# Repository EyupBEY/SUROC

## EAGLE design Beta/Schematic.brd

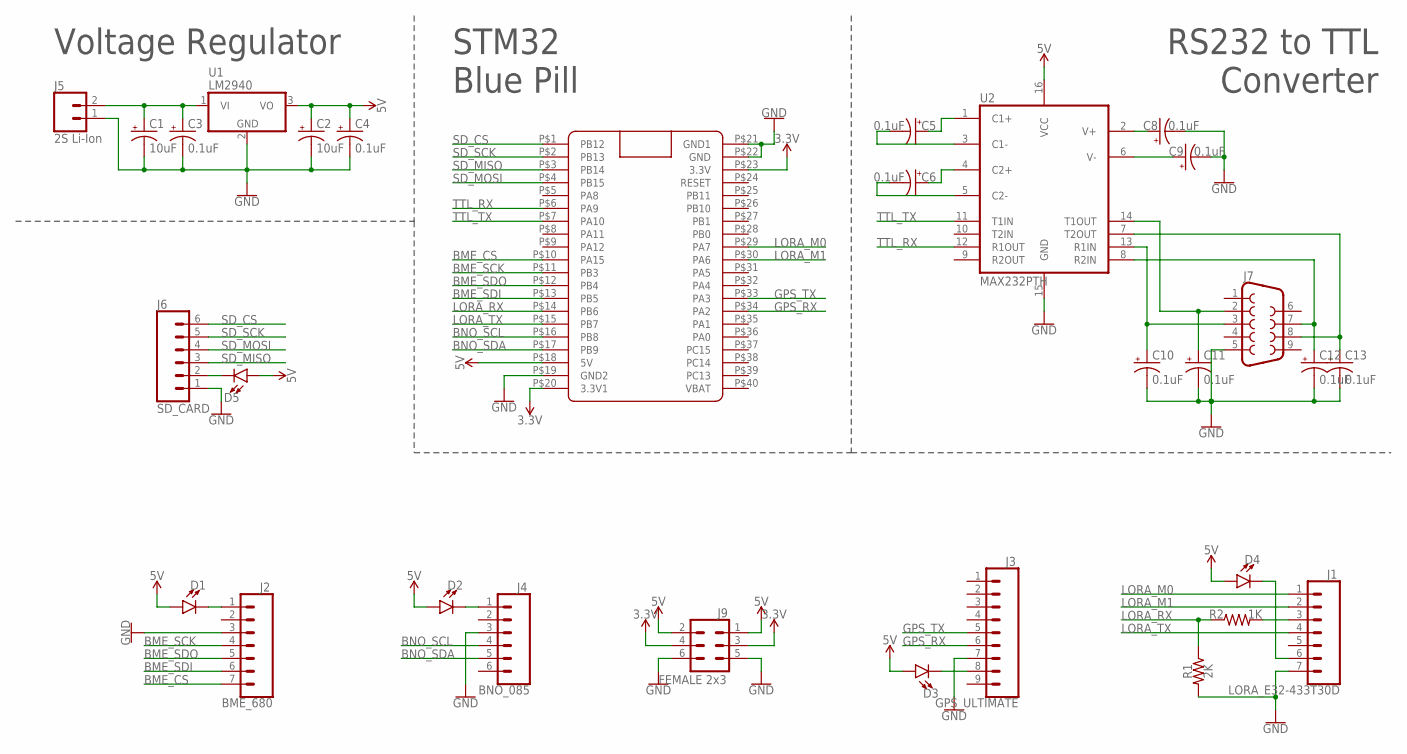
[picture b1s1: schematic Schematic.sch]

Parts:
C1, C2: 10uF; CPOL-RADIAL-2.5MM-5MM-KIT
C3, C4, C5, C6, C8, C9, C10, C11, C12, C13: 0.1uF; CPOL-RADIAL-2.5MM-5MM-KIT
D1, D2, D3, D4, D5: LED-3MM-NO_SILK; LED_3MM-NS
J1: LORA_E32-433T30D; 1X07
J2: BME_680; 1X07
J3: GPS_ULTIMATE; 1X09
J4: BNO_085; 1X06
J5: 2S Li-Ion; 1X02
J6: SD_CARD; 1X06
J7: DB9FEMALE; DB9
J9: FEMALE 2x3; 2X3
R1: 2K; AXIAL-0.1-KIT
R2: 1K; AXIAL-0.1-KIT
STM32BLUEPILL: STM32 Blue Pill; BLUE_PILL
U1: LM2940; TO220V
U2: MAX232PTH; DIL16

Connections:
3.3V: J9.3, J9.4, STM32BLUEPILL.P$20 (3.3V1), STM32BLUEPILL.P$23 (3.3V)
5V: C2.1 (+), C4.1 (+), D1.A, D2.A, D3.A, D4.A, D5.A, J9.1, J9.2, STM32BLUEPILL.P$18 (5V), U1.3 (VO), U2.16 (VCC)
BME_CS: J2.7, STM32BLUEPILL.P$10 (PA15)
BME_SCK: J2.4, STM32BLUEPILL.P$11 (PB3)
BME_SDI: J2.6, STM32BLUEPILL.P$13 (PB5)
BME_SDO: J2.5, STM32BLUEPILL.P$12 (PB4)
BNO_SCL: J4.4, STM32BLUEPILL.P$16 (PB8)
BNO_SDA: J4.5, STM32BLUEPILL.P$17 (PB9)
GND: C1.2 (-), C2.2 (-), C3.2 (-), C4.2 (-), C8.2 (-), C9.2 (-), C10.2 (-), C11.2 (-), C12.2 (-), C13.2 (-), J1.7, J2.3, J3.7, J4.3, J5.1, J6.1, J7.5, J9.5, J9.6, R1.P$2 (2), STM32BLUEPILL.P$19 (GND2), STM32BLUEPILL.P$21 (GND1), STM32BLUEPILL.P$22 (GND), U1.2 (GND), U2.15 (GND)
GPS_RX: J3.6, STM32BLUEPILL.P$34 (PA2)
GPS_TX: J3.5, STM32BLUEPILL.P$33 (PA3)
LORA_M0: J1.1, STM32BLUEPILL.P$29 (PA7)
LORA_M1: J1.2, STM32BLUEPILL.P$30 (PA6)
LORA_RX: R1.P$1 (1), R2.P$1 (1), STM32BLUEPILL.P$14 (PB6)
LORA_TX: J1.4, STM32BLUEPILL.P$15 (PB7)
unnamed: C1.1 (+), C3.1 (+), J5.2, U1.1 (VI)
unnamed: C8.1 (+), U2.2 (V+)
unnamed: C9.1 (+), U2.6 (V-)
unnamed: J1.3, R2.P$2 (2)
unnamed: D1.K (C), J2.1
unnamed: D2.K (C), J4.1
unnamed: D3.K (C), J3.8
unnamed: C6.1 (+), U2.4 (C2+)
unnamed: C6.2 (-), U2.5 (C2-)
unnamed: C5.1 (+), U2.1 (C1+)
unnamed: C5.2 (-), U2.3 (C1-)
unnamed: D4.K (C), J1.6
unnamed: C13.1 (+), J7.8, U2.7 (T2OUT)
unnamed: C12.1 (+), J7.7, U2.8 (R2IN)
unnamed: C11.1 (+), J7.2, U2.14 (T1OUT)
unnamed: C10.1 (+), J7.3, U2.13 (R1IN)
unnamed: D5.K (C), J6.2
SD_CS: J6.6, STM32BLUEPILL.P$1 (PB12)
SD_MISO: J6.3, STM32BLUEPILL.P$3 (PB14)
SD_MOSI: J6.4, STM32BLUEPILL.P$4 (PB15)
SD_SCK: J6.5, STM32BLUEPILL.P$2 (PB13)
TTL_RX: STM32BLUEPILL.P$6 (PA9), U2.12 (R1OUT)
TTL_TX: STM32BLUEPILL.P$7 (PA10), U2.11 (T1IN)

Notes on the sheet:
RS232 to TTL Converter
STM32 Blue Pill
Voltage Regulator

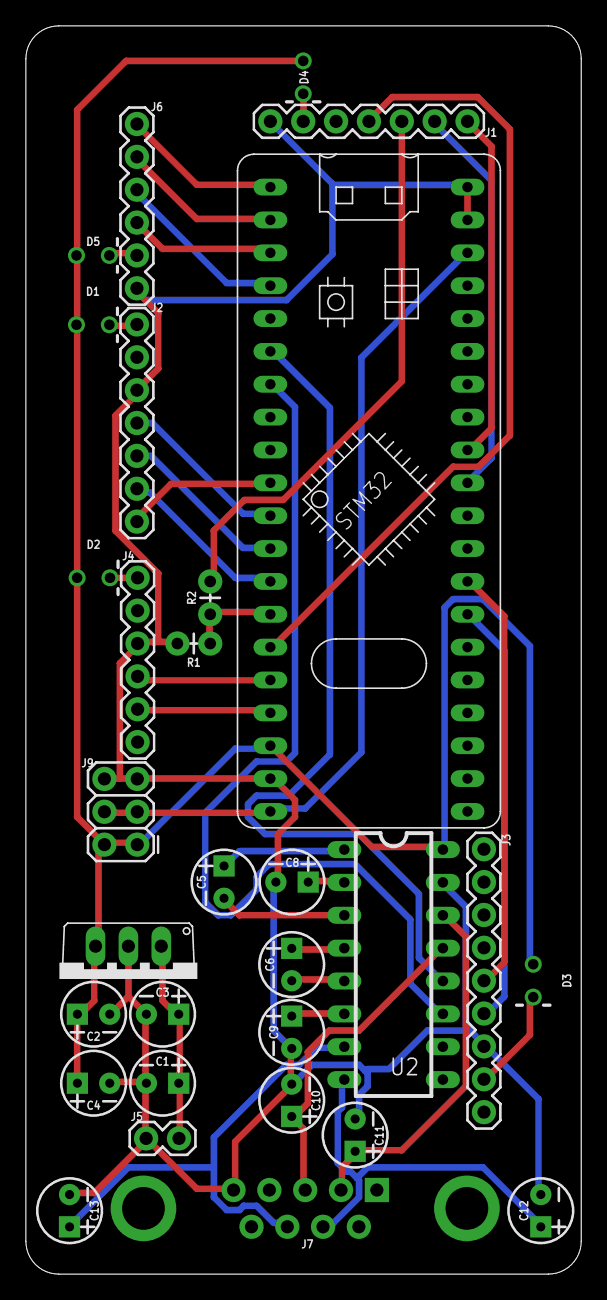
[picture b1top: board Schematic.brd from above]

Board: 2 copper layers, 42.9 x 96.5 mm, 30 parts (0 on the bottom side), 38 nets.

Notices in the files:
parts and their libraries:
SparkFun-Capacitors: Licensing: Creative Commons ShareAlike 4.0 International - https://creativecommons.org/licenses/by-sa/4.0
